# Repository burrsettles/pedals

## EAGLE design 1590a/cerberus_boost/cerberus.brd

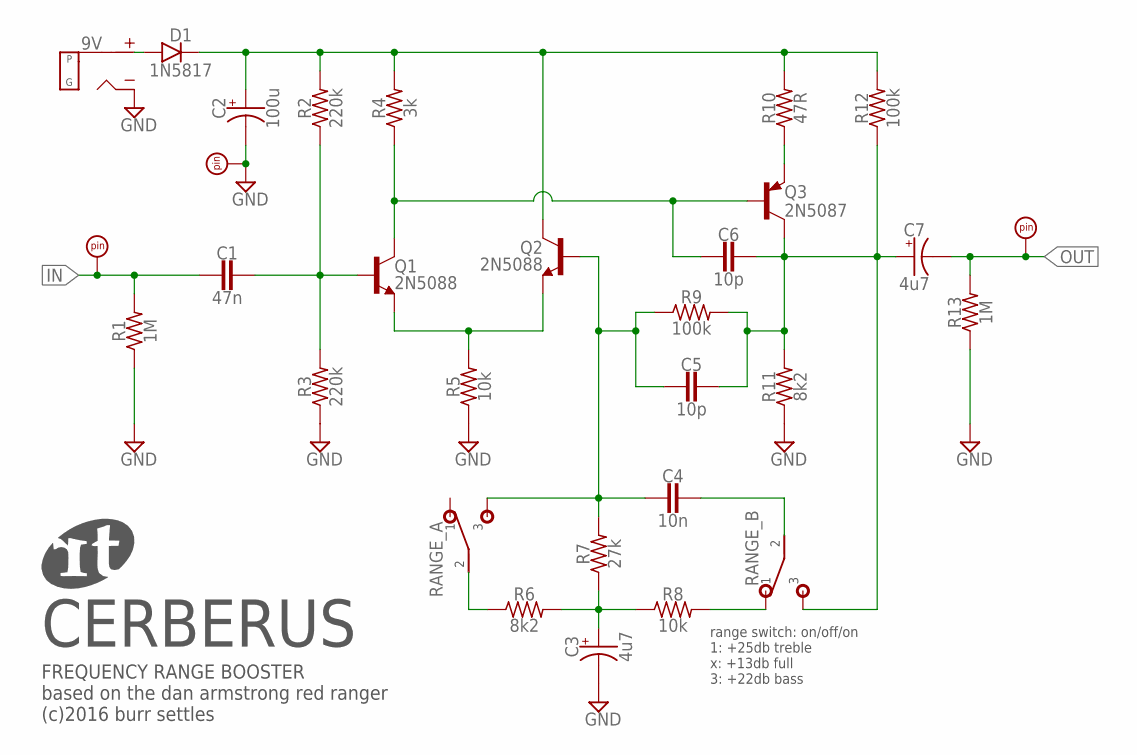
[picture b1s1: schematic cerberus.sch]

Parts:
9V: DC_MONO; DC
C1: 47n; BOX_SMALL
C2: 100u; 050_020_1
C3, C7: 4u7; 050_020_1
C4: 10n; BOX_SMALL
C5, C6: 10p; 050X030_025_2
D1: 1N5817; DO41-3
GND: PADRND; ROUND
IN: PADSQR; SQUARE
OUT: PADSQR; SQUARE
Q1, Q2: 2N5088; TO92-
Q3: 2N5087; TO92-
R1, R13: 1M; R0207/3
R2, R3: 220k; R0207/3
R4: 3k; R0207/3
R5, R8: 10k; R0207/3
R6, R11: 8k2; R0207/3
R7: 27k; R0207/3
R9, R12: 100k; R0207/3
R10: 47R; R0207/3
RANGE: DPDT; DPDT_PADS

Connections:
GND: 9V.S (SLEEVE), C2.-, C3.-, GND.1, R1.1, R3.1, R5.1, R11.1, R13.1
IN: C1.2, IN.1, R1.2
unnamed: C1.1, Q1.2 (B), R2.1, R3.2
unnamed: Q3.3 (E), R10.1
unnamed: 9V.T (TIP), D1.A
unnamed: C6.2, Q1.1 (C), Q3.2 (B), R4.1
unnamed: Q1.3 (E), Q2.3 (E), R5.2
unnamed: C5.1, C6.1, C7.+, Q3.1 (C), R9.2, R11.2, R12.1, RANGE.P$6 (3)
unnamed: C2.+, D1.C, Q2.1 (C), R2.2, R4.2, R10.2, R12.2
unnamed: R6.1, RANGE.P$2 (2)
unnamed: C4.1, RANGE.P$5 (2)
unnamed: C4.2, C5.2, Q2.2 (B), R7.2, R9.1, RANGE.P$3 (3)
unnamed: C3.+, R6.2, R7.1, R8.1
unnamed: R8.2, RANGE.P$4 (1)
OUT: C7.-, OUT.1, R13.2

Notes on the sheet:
CERBERUS
FREQUENCY RANGE BOOSTER based on the dan armstrong red ranger (c)2016 burr settles
range switch: on/off/on 1: +25db treble x: +13db full 3: +22db bass

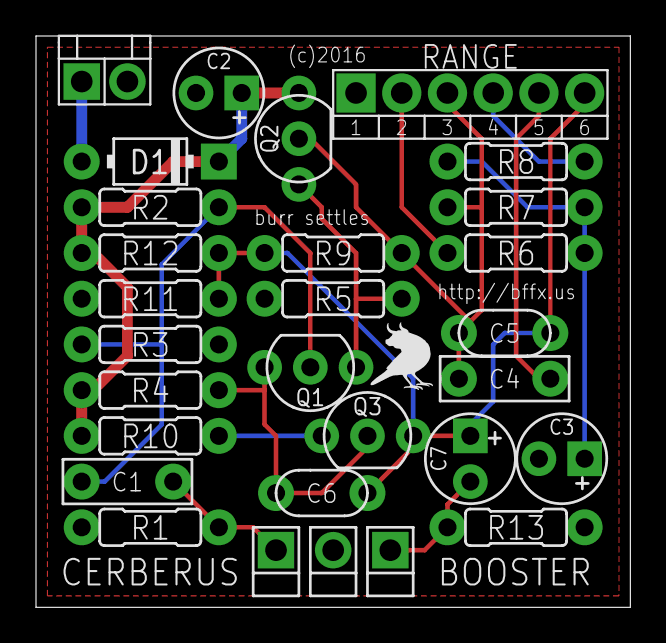
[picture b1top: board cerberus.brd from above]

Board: 2 copper layers, 33.0 x 31.7 mm, 30 parts (1 on the bottom side), 15 nets.

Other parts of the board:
U$1: BF0150

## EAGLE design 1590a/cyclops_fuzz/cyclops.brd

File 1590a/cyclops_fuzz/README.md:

# CYCLOPS

**MUFFLIKE FUZZ**

© 2016 Burr Settles ([LICENSE](../../LICENSE.md))

### overview

CYCLOPS is an in-your-face, no-holds-barred, wall-of-sound machine in a tiny little box. It is based on the [runoffgroove 22/7](http://runoffgroove.com/22-7.html), which in turn is a CMOS implementation of the [EHX Big Muff Pi](https://en.wikipedia.org/wiki/Big_Muff). However, CYCLOPS has been modified to have nothing but a VOLUME control: the tone stack has been removed (no more scooped mids!), and the gain/sustain is designed to be an internal trimmer; just to "set it and forget it" to taste.

### notes

* The clipping diodes (D1-D4) can be anything you want, though 1N914 is common in BMP clones. In my build, I ended up using 3mm red LEDs for D1-D2, and 1N4148s for D3-D4.
* The GAIN knob is layed out as a trimmer, but you can wire it to an offboard pot if you prefer.
* IC1 pins 2, 4, 13, and 16 are not connected.

### bill of materials

Qty | Parts | Value
--- | ----- | -----
1 | C1 | 47n film
1 | C2 | 100u electrolytic
1 | C3 | 220p ceramic
5 | C4, C5, C7, C9, C11 | 100n film
3 | C6, C8, C10 | 150p ceramic
4 | D1, D2, D3, D4 | your choice
1 | D5 | 1N5417
1 | IC1 | CD4049 hex-inverting buffer
3 | R1, R2, R9 | 100k
4 | R3, R6, R8, R11 | 1M
1 | R4 | 1k
2 | R5, R7 | 33k
1 | R10 | 330k
1 | GAIN | 100kA (trimmer)
1 | VOLUME | 100kA

### schematic

### layout

1.3" x 1.46" (1590a)

### build pic

18 June 2016

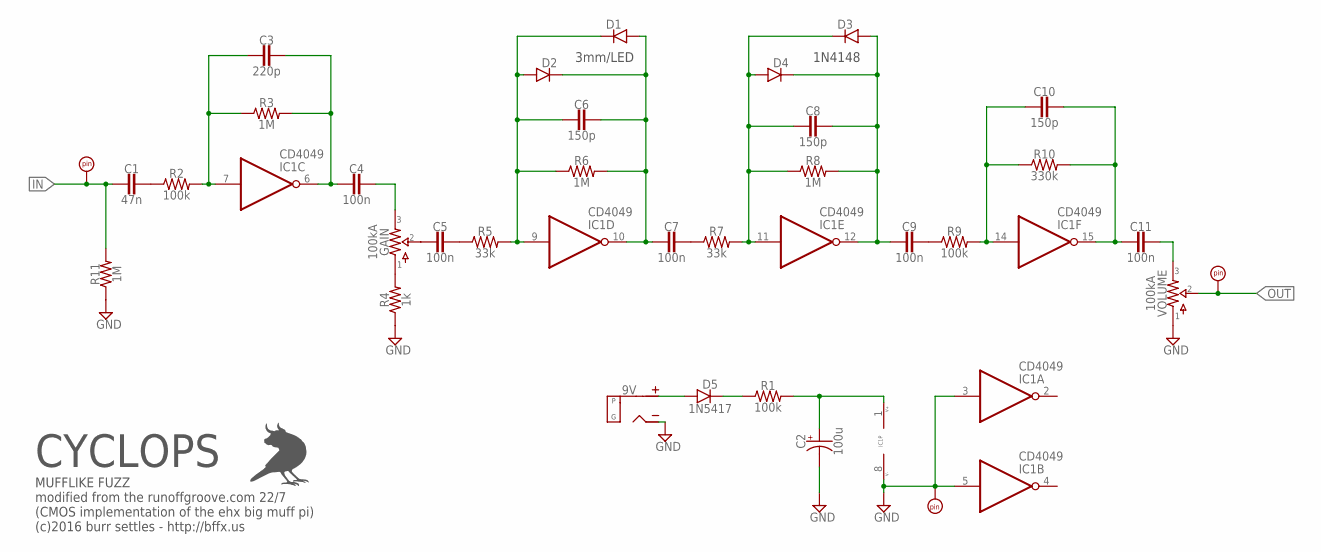
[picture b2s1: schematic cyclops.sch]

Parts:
9V: DC_MONO; DC
C1: 47n; 050X030_025_2
C2: 100u; 063_025
C3: 220p; 050X030_025_2
C4, C5, C7, C9, C11: 100n; 050X030_025_2
C6, C8, C10: 150p; 050X030_025_2
D1, D2, D3, D4: DO41.2; DO41-2
D5: 1N5417; DO41-3
GAIN: 100kA; 2262_TRIM
GND: PADRND; ROUND
IC1: CD4049; DIL16
IN: PADSQR; SQUARE
OUT: PADSQR; SQUARE
R1, R2, R9: 100k; R0207/2V
R3, R6, R8, R11: 1M; R0207/2V
R4: 1k; R0207/2V
R5, R7: 33k; R0207/2V
R10: 330k; R0207/2V
VOLUME: 100kA; PADS_SMALL

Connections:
GND: 9V.S (SLEEVE), C2.-, GND.1, IC1.3 (I), IC1.5 (I), IC1.8 (VSS), R4.1, R11.1, VOLUME.1
IN: C1.2, IN.1, R11.2
unnamed: C3.1, C4.2, IC1.6 (O), R3.2
unnamed: C5.2, GAIN.2
unnamed: C3.2, IC1.7 (I), R2.2, R3.1
unnamed: C1.1, R2.1
unnamed: C5.1, R5.1
unnamed: C6.2, D1.C, D2.A, IC1.9 (I), R5.2, R6.1
unnamed: C6.1, C7.2, D1.A, D2.C, IC1.10 (O), R6.2
unnamed: C7.1, R7.1
unnamed: C8.2, D3.C, D4.A, IC1.11 (I), R7.2, R8.1
unnamed: C4.1, GAIN.3
unnamed: C8.1, C9.2, D3.A, D4.C, IC1.12 (O), R8.2
unnamed: C9.1, R9.1
unnamed: C10.2, IC1.14 (I), R9.2, R10.1
unnamed: C10.1, C11.2, IC1.15 (O), R10.2
unnamed: GAIN.1, R4.2
unnamed: C11.1, VOLUME.3
unnamed: 9V.T (TIP), D5.A
unnamed: C2.+, IC1.1 (VDD), R1.2
unnamed: D5.C, R1.1
OUT: OUT.1, VOLUME.2

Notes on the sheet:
3mm/LED
1N4148
CYCLOPS
MUFFLIKE FUZZ modified from the runoffgroove.com 22/7 (CMOS implementation of the ehx big muff pi) (c)2016 burr settles - http://bffx.us

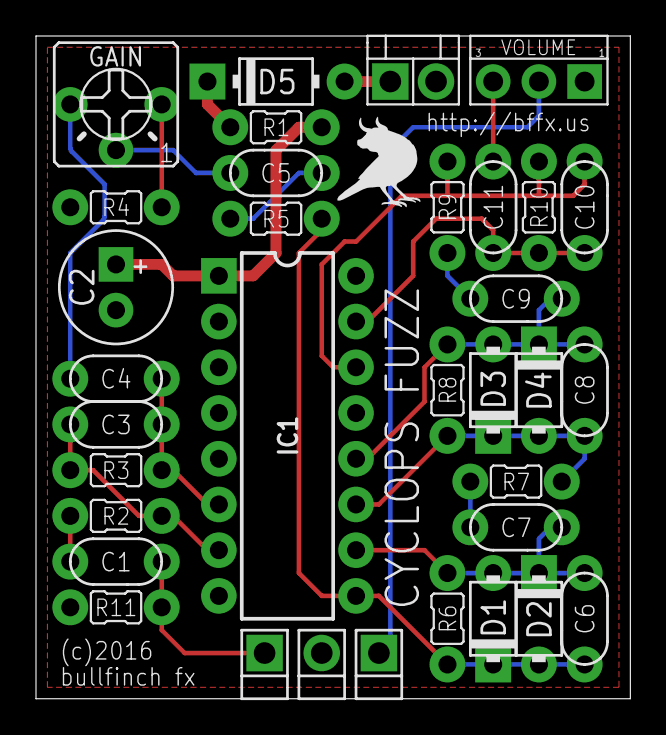
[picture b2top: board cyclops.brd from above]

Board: 2 copper layers, 33.0 x 36.8 mm, 35 parts (1 on the bottom side), 22 nets.

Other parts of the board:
U$3: BF0200

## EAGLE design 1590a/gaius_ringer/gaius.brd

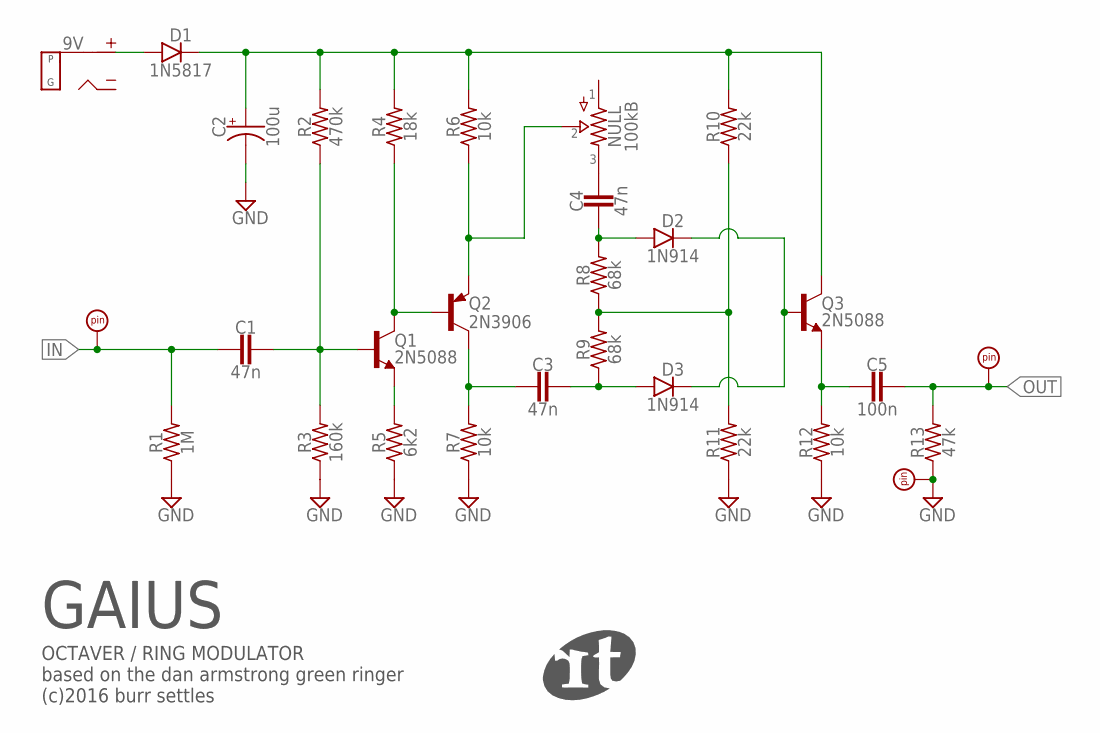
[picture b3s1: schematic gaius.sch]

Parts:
9V: DC_MONO; DC
C1, C3, C4: 47n; 050X030_025_2
C2: 100u; 050_020_1
C5: 100n; 050X030_025_2
D1: 1N5817; DO41-3
D2, D3: 1N914; DO35-2
GND: PADRND; ROUND
IN: PADSQR; SQUARE
NULL: 100kB; 2262_TRIM
OUT: PADSQR; SQUARE
Q1, Q3: 2N5088; TO92-
Q2: 2N3906; TO92-
R1: 1M; R0207/3
R2: 470k; R0207/3
R3: 160k; R0207/3
R4: 18k; R0207/3
R5: 6k2; R0207/3
R6, R7, R12: 10k; R0207/3
R8, R9: 68k; R0207/3
R10, R11: 22k; R0207/3
R13: 47k; R0207/3

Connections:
GND: C2.-, GND.1, R1.1, R3.1, R5.1, R7.1, R11.1, R12.1, R13.1
IN: C1.2, IN.1, R1.2
unnamed: Q1.1 (C), Q2.2 (B), R4.1
unnamed: Q1.3 (E), R5.2
unnamed: C1.1, Q1.2 (B), R2.1, R3.2
unnamed: C4.2, D2.A, R8.2
unnamed: NULL.2, Q2.3 (E), R6.1
unnamed: R8.1, R9.2, R10.1, R11.2
unnamed: C4.1, NULL.3
unnamed: C3.2, Q2.1 (C), R7.2
unnamed: C3.1, D3.A, R9.1
unnamed: C5.2, Q3.3 (E), R12.2
unnamed: D2.C, D3.C, Q3.2 (B)
unnamed: C2.+, D1.C, Q3.1 (C), R2.2, R4.2, R6.2, R10.2
unnamed: 9V.T (TIP), D1.A
OUT: C5.1, OUT.1, R13.2

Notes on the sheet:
GAIUS
OCTAVER / RING MODULATOR based on the dan armstrong green ringer (c)2016 burr settles

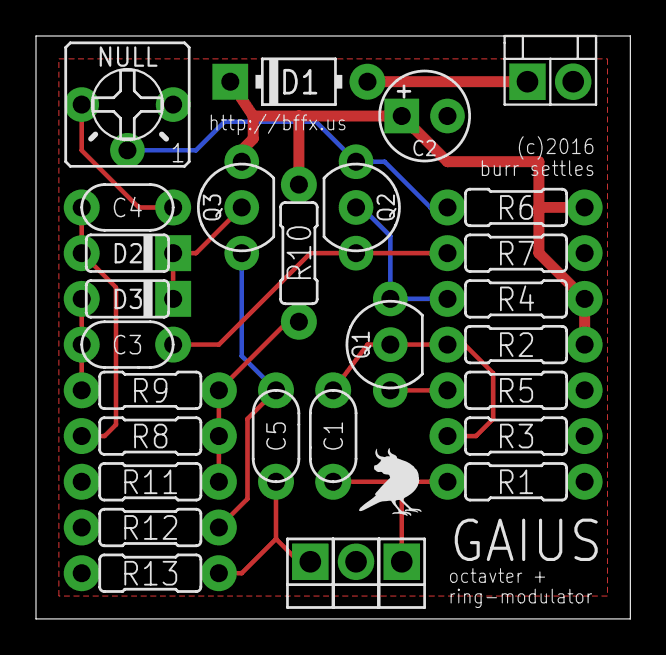
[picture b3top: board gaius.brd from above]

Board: 2 copper layers, 33.0 x 32.4 mm, 30 parts (1 on the bottom side), 16 nets.

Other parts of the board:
U$1: BF0150

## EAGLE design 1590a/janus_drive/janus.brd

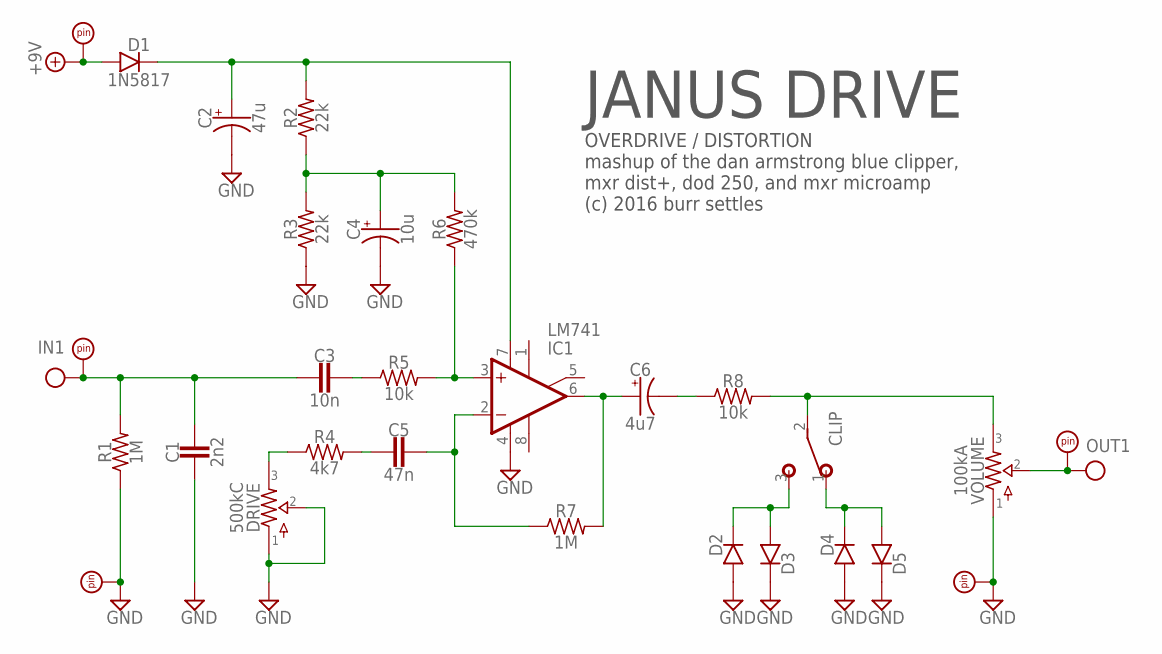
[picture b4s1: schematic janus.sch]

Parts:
C1: 2n2; BOX_SMALL
C2: 47u; 050_020_1
C3: 10n; BOX_SMALL
C4: 10u; 050_020_1
C5: 47n; BOX_SMALL
C6: 4u7; 050_020_1
CLIP: SPDTPADS; SPDT
D1: 1N5817; DO41-2
D2, D3: DO35.2; DO35-2
D4, D5: DO35.3; DO35-3
DRIVE: 500kC; PADS_SMALL
IC1: LM741; DIL08
PAD1, PAD2, PAD5: PADSQR; SQUARE
PAD3, PAD4: PADRND; ROUND
R1, R7: 1M; R0207/3
R2, R3: 22k; R0207/3
R4: 4k7; R0207/3
R5, R8: 10k; R0207/3
R6: 470k; R0207/3
VOLUME: 100kA; PADS_SMALL

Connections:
+9V: D1.A, PAD1.1
CLIP: CLIP.2, R8.2, VOLUME.3
GND: C1.1, C2.-, C4.-, D2.A, D3.C, D4.A, D5.C, DRIVE.1, DRIVE.2, IC1.4 (V-), PAD3.1, PAD4.1, R1.1, R3.1, VOLUME.1
IN: C1.2, C3.2, PAD2.1, R1.2
unnamed: C3.1, R5.1
unnamed: IC1.3 (+IN), R5.2, R6.1
unnamed: C5.1, IC1.2 (-IN), R7.1
unnamed: C5.2, R4.2
unnamed: C6.+, IC1.6 (OUT), R7.2
unnamed: C6.-, R8.1
unnamed: CLIP.3 (S), D2.C, D3.A
unnamed: C4.+, R2.1, R3.2, R6.2
unnamed: CLIP.1 (O), D4.C, D5.A
unnamed: DRIVE.3, R4.1
unnamed: C2.+, D1.C, IC1.7 (V+), R2.2
OUT: PAD5.1, VOLUME.2

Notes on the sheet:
JANUS DRIVE
OVERDRIVE / DISTORTION mashup of the dan armstrong blue clipper, mxr dist+, dod 250, and mxr microamp (c) 2016 burr settles

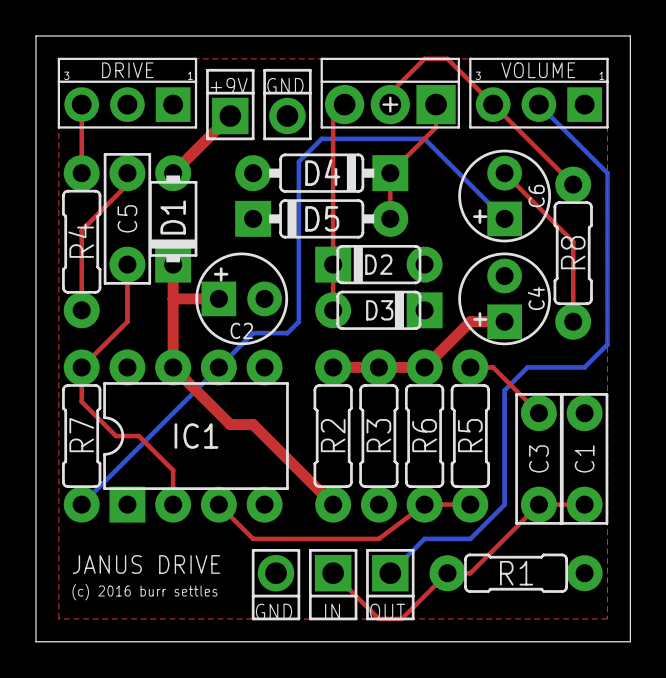
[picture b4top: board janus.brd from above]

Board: 2 copper layers, 33.0 x 33.7 mm, 28 parts (1 on the bottom side), 16 nets.

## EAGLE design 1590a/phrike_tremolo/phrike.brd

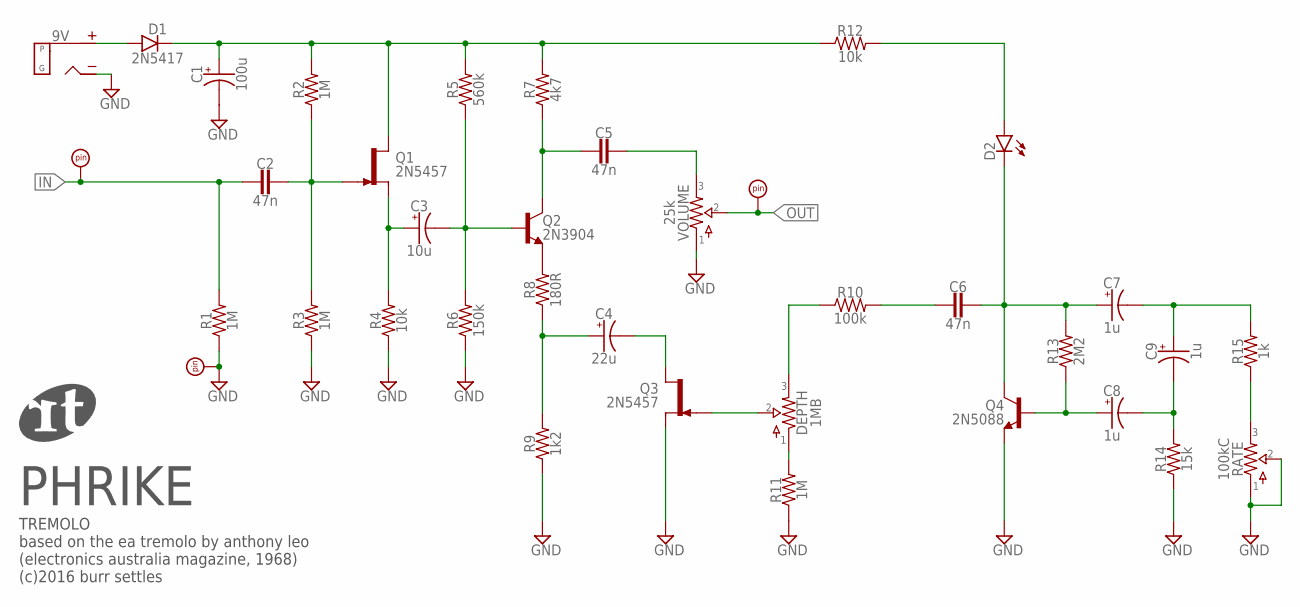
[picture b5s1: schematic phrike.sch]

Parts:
9V: DC_MONO; DC
C1: 100u; 063_025
C2, C5, C6: 47n; 050X030_025_2
C3: 10u; 050_020_1
C4: 22u; 050_020_1
C7, C8, C9: 1u; 050_020_1
D1: 2N5417; DO41-3
D2: LEDA; 3MM_A
DEPTH: 1MB; 2262_TRIM
GND: PADRND; ROUND
IN: PADSQR; SQUARE
OUT: PADSQR; SQUARE
Q1, Q3: 2N5457; TO92-
Q2: 2N3904; TO92-L2
Q4: 2N5088; TO92-
R1, R2, R3, R11: 1M; R0207/3
R4, R12: 10k; R0207/3
R5: 560k; R0207/3
R6: 150k; R0207/3
R7: 4k7; R0207/3
R8: 180R; R0207/3
R9: 1k2; R0207/3
R10: 100k; R0207/3
R13: 2M2; R0207/3
R14: 15k; R0207/3
R15: 1k; R0207/3
RATE: 100kC; PADS_SMALL
VOLUME: 25k; 2262_TRIM

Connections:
+9V: 9V.T (TIP), D1.A
GND: 9V.S (SLEEVE), C1.-, GND.1, Q3.2 (S), Q4.3 (E), R1.1, R3.1, R4.1, R6.1, R9.1, R11.1, R14.1, RATE.1, RATE.2, VOLUME.1
IN: C2.2, IN.1, R1.2
unnamed: C2.1, Q1.1 (G), R2.1, R3.2
unnamed: C3.+, Q1.2 (S), R4.2
unnamed: C3.-, Q2.2 (B), R5.1, R6.2
unnamed: C5.2, Q2.1 (C), R7.1
unnamed: Q2.3 (E), R8.2
unnamed: C5.1, VOLUME.3
unnamed: C1.+, D1.C, Q1.3 (D), R2.2, R5.2, R7.2, R12.1
unnamed: C4.+, R8.1, R9.2
unnamed: C4.-, Q3.3 (D)
unnamed: DEPTH.2, Q3.1 (G)
unnamed: DEPTH.3, R10.1
unnamed: C6.2, R10.2
unnamed: C6.1, C7.+, D2.K (C), Q4.1 (C), R13.2
unnamed: C8.+, Q4.2 (B), R13.1
unnamed: C7.-, C9.+, R15.2
unnamed: C8.-, C9.-, R14.2
unnamed: DEPTH.1, R11.2
unnamed: R15.1, RATE.3
unnamed: D2.A, R12.2
OUT: OUT.1, VOLUME.2

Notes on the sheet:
PHRIKE
TREMOLO based on the ea tremolo by anthony leo (electronics australia magazine, 1968) (c)2016 burr settles

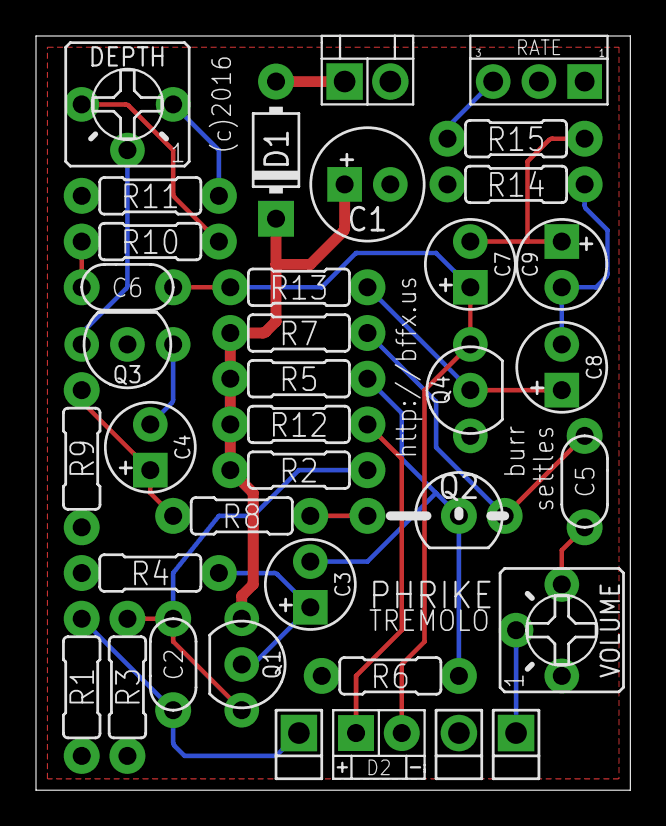
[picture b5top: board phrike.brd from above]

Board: 2 copper layers, 33.0 x 41.9 mm, 38 parts (1 on the bottom side), 23 nets.

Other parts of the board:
U$1: BF0150

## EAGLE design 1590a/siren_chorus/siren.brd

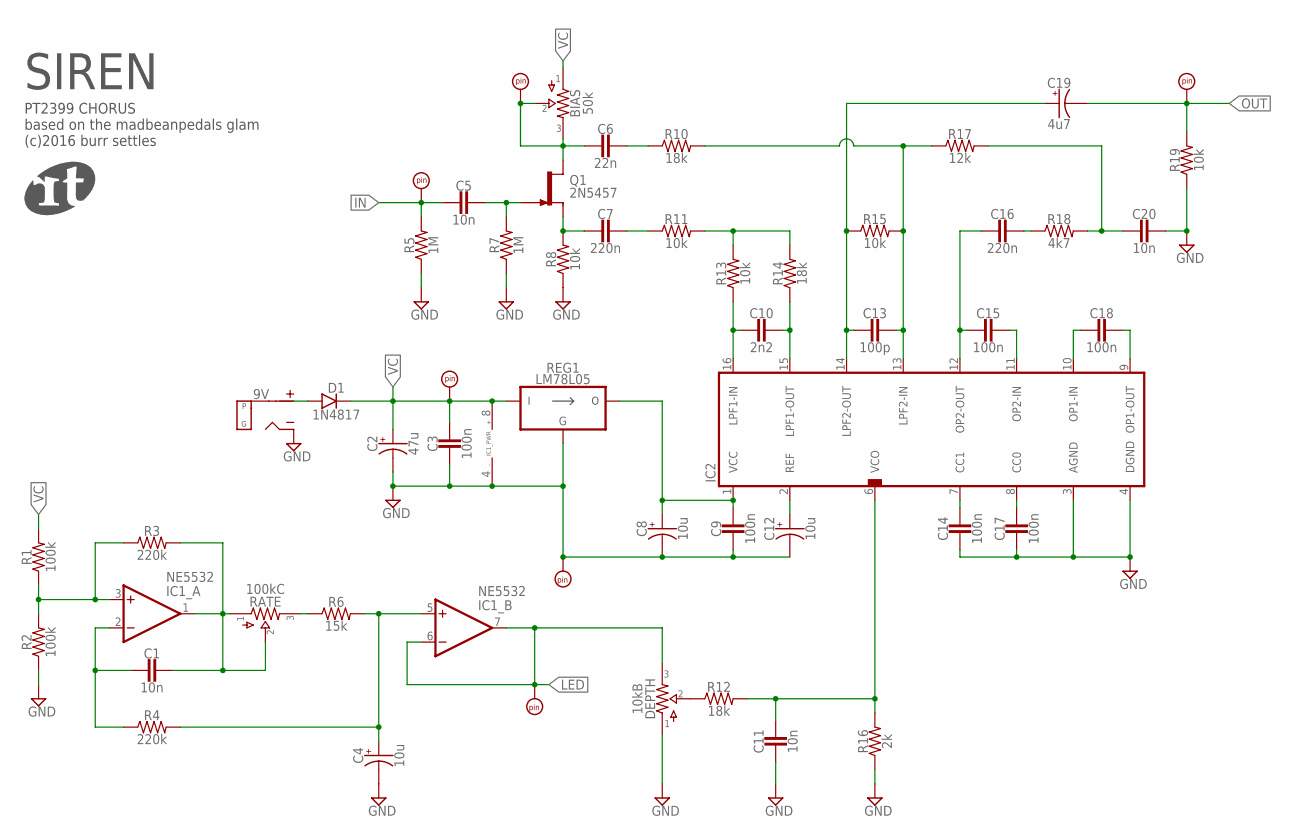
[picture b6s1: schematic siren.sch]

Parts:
9V: DC_MONO; DC
BIAS: 50k; 2262_TRIM
C1, C5, C11, C20: 10n; 050X030_025_2
C2: 47u; 050_020_1
C3, C9, C14, C15, C17, C18: 100n; 050X030_025_2
C4, C12: 10u; 050_020_1
C6: 22n; 050X030_025_2
C7, C16: 220n; 050X030_025_2
C8: 10u; 050_020
C10: 2n2; 050X030_025_2
C13: 100p; 050X030_025_2
C19: 4u7; 050_020_1
D1: 1N4817; DO41-3
DEPTH: 10kB; 2262_TRIM
GND: PADRND; ROUND
IC1: NE5532; DIL08
IC2: PT2399TH; DIL16
IN: PADSQR; SQUARE
L+: PADSQR; SQUARE
OUT: PADSQR; SQUARE
PAD1, PAD2: PAD; UNLABELED
Q1: 2N5457; TO92-
R1, R2: 100k; R0207/2V
R3, R4: 220k; R0207/2V
R5, R7: 1M; R0207/2V
R6: 15k; R0207/2V
R8, R11, R13, R15, R19: 10k; R0207/2V
R10, R12, R14: 18k; R0207/2V
R16: 2k; R0207/2V
R17: 12k; R0207/2V
R18: 4k7; R0207/2V
RATE: 100kC; PADS_SMALL
REG1: LM78L05; TO92-

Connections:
+9V: 9V.T (TIP), D1.A
GND: 9V.S (SLEEVE), C2.-, C3.2, C4.-, C8.-, C9.2, C11.2, C12.-, C14.2, C17.2, C20.1, DEPTH.1, GND.1, IC1.4 (V-), IC2.3 (AGND), IC2.4 (DGND), R2.1, R5.1, R7.1, R8.1, R16.1, R19.1, REG1.2 (GND)
IN: C5.2, IN.1, R5.2
LED: DEPTH.3, IC1.6 (-IN), IC1.7 (OUT), L+.1
unnamed: C13.1, IC2.13 (LPF2-IN), R10.2, R15.2, R17.1
unnamed: C8.+, C9.1, IC2.1 (VCC), REG1.3 (VO)
unnamed: C10.2, IC2.16 (LPF1-IN), R13.1
unnamed: C10.1, IC2.15 (LPF1-OUT), R14.1
unnamed: C20.2, R17.2, R18.2
unnamed: C12.+, IC2.2 (REF)
unnamed: C14.1, IC2.7 (CC1)
unnamed: C17.1, IC2.8 (CC0)
unnamed: C15.1, IC2.11 (OP2-IN)
unnamed: C18.2, IC2.10 (OP1-IN)
unnamed: C18.1, IC2.9 (OP1-OUT)
unnamed: C13.2, C19.+, IC2.14 (LPF2-OUT), R15.1
unnamed: R11.2, R13.2, R14.2
unnamed: C7.1, R11.1
unnamed: C7.2, Q1.2 (S), R8.2
unnamed: C6.1, R10.1
unnamed: BIAS.2, BIAS.3, C6.2, PAD2.P$1, Q1.3 (D)
unnamed: C5.1, Q1.1 (G), R7.2
unnamed: IC1.3 (+IN), R1.1, R2.2, R3.1
unnamed: C15.2, C16.2, IC2.12 (OP2-OUT)
unnamed: C16.1, R18.1
unnamed: C1.1, IC1.1 (OUT), R3.2, RATE.1, RATE.2
unnamed: C1.2, IC1.2 (-IN), R4.1
unnamed: DEPTH.2, R12.1
unnamed: R6.1, RATE.3
unnamed: C4.+, IC1.5 (+IN), R4.2, R6.2
unnamed: C11.1, IC2.6 (VCO), R12.2, R16.2
OUT: C19.-, OUT.1, R19.2
VC: BIAS.1, C2.+, C3.1, D1.C, IC1.8 (V+), PAD1.P$1, R1.2, REG1.1 (VI)

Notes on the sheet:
PT2399 CHORUS based on the madbeanpedals glam (c)2016 burr settles
SIREN

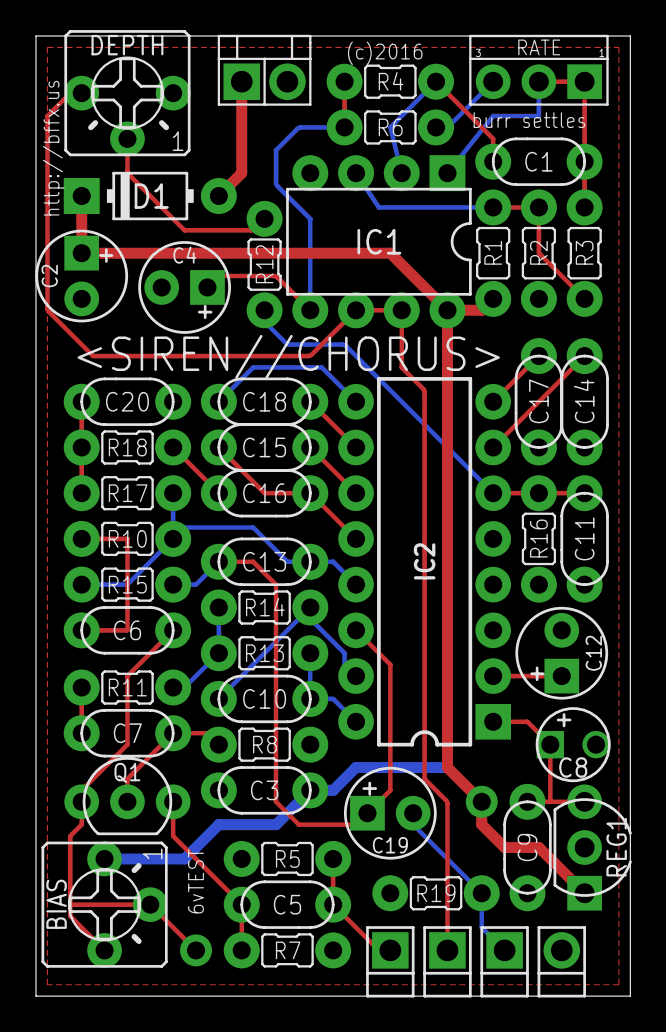
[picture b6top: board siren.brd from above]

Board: 2 copper layers, 33.0 x 53.3 mm, 54 parts (1 on the bottom side), 33 nets.

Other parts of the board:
U$1: BF0150

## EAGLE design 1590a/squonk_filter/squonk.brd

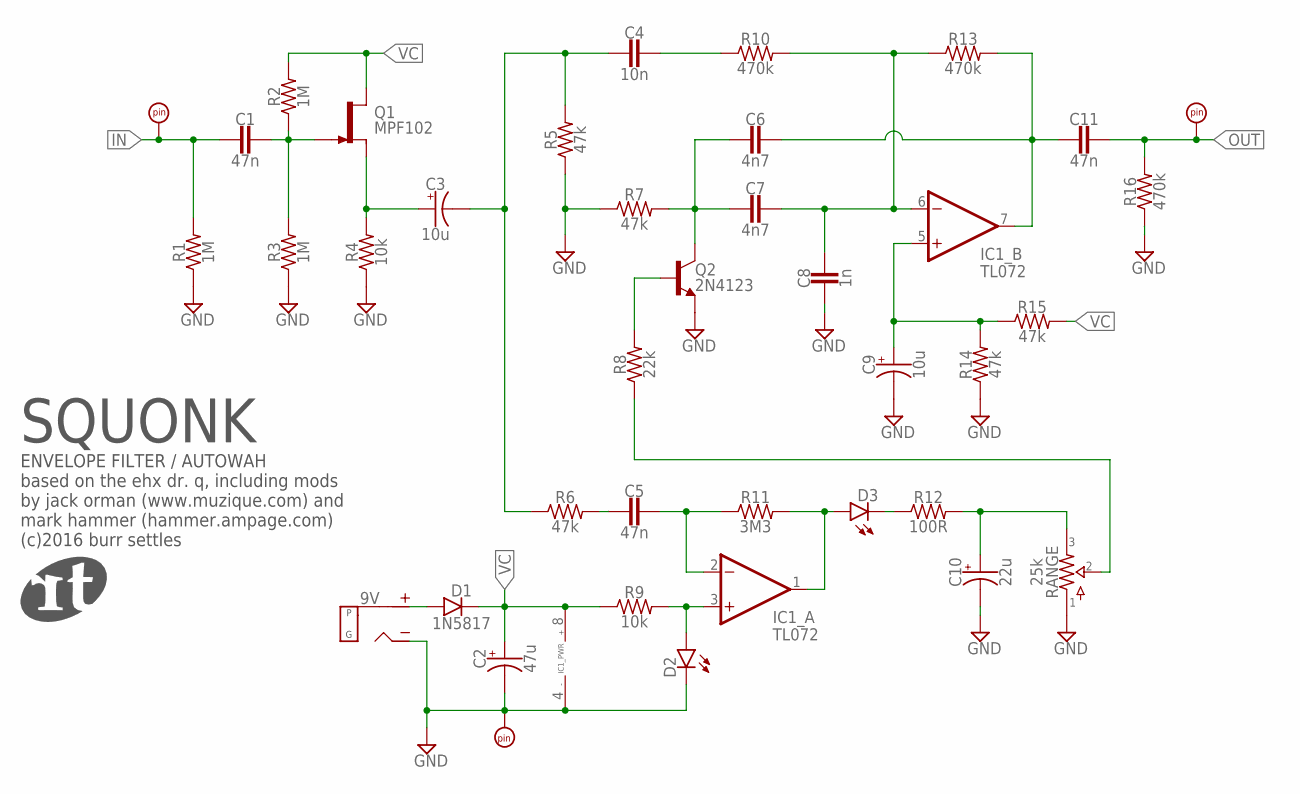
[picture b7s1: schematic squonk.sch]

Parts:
9V: DC_MONO; DC
C1, C5, C11: 47n; 050X030_025_2
C2: 47u; 050_020_1
C3, C9: 10u; 050_020_1
C4: 10n; 050X030_025_2
C6, C7: 4n7; 050X030_025_2
C8: 1n; 050X030_025_2
C10: 22u; 050_020_1
D1: 1N5817; DO41-3
D2, D3: LEDB; 3MM_B
GND: PADRND; ROUND
IC1: TL072; DIL08
IN: PADSQR; SQUARE
OUT: PADSQR; SQUARE
Q1: MPF102; TO92-
Q2: 2N4123; TO92-
R1, R2, R3: 1M; R0207/3
R4, R9: 10k; R0207/3
R5, R6, R7, R14, R15: 47k; R0207/3
R8: 22k; R0207/3
R10, R13, R16: 470k; R0207/3
R11: 3M3; R0207/3
R12: 100R; R0207/3
RANGE: 25k; PADS_SMALL

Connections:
GND: 9V.S (SLEEVE), C2.-, C8.2, C9.-, C10.-, D2.K (C), GND.1, IC1.4 (V-), Q2.3 (E), R1.1, R3.1, R4.1, R5.1, R7.1, R14.1, R16.1, RANGE.1
IN: C1.2, IN.1, R1.2
unnamed: C1.1, Q1.1 (G), R2.1, R3.2
unnamed: C3.+, Q1.2 (S), R4.2
unnamed: C3.-, C4.2, R5.2, R6.1
unnamed: C5.2, R6.2
unnamed: D2.A, IC1.3 (+IN), R9.2
unnamed: C5.1, IC1.2 (-IN), R11.1
unnamed: D3.A, IC1.1 (OUT), R11.2
unnamed: D3.K (C), R12.1
unnamed: C10.+, R12.2, RANGE.3
unnamed: 9V.T (TIP), D1.A
unnamed: C7.1, C8.1, IC1.6 (-IN), R10.2, R13.1
unnamed: Q2.2 (B), R8.2
unnamed: R8.1, RANGE.2
unnamed: C6.2, C7.2, Q2.1 (C), R7.2
unnamed: C6.1, C11.2, IC1.7 (OUT), R13.2
unnamed: C4.1, R10.1
unnamed: C9.+, IC1.5 (+IN), R14.2, R15.1
OUT: C11.1, OUT.1, R16.2
VC: C2.+, D1.C, IC1.8 (V+), Q1.3 (D), R2.2, R9.1, R15.2

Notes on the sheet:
SQUONK
ENVELOPE FILTER / AUTOWAH based on the ehx dr. q, including mods by jack orman (www.muzique.com) and mark hammer (hammer.ampage.com) (c)2016 burr settles

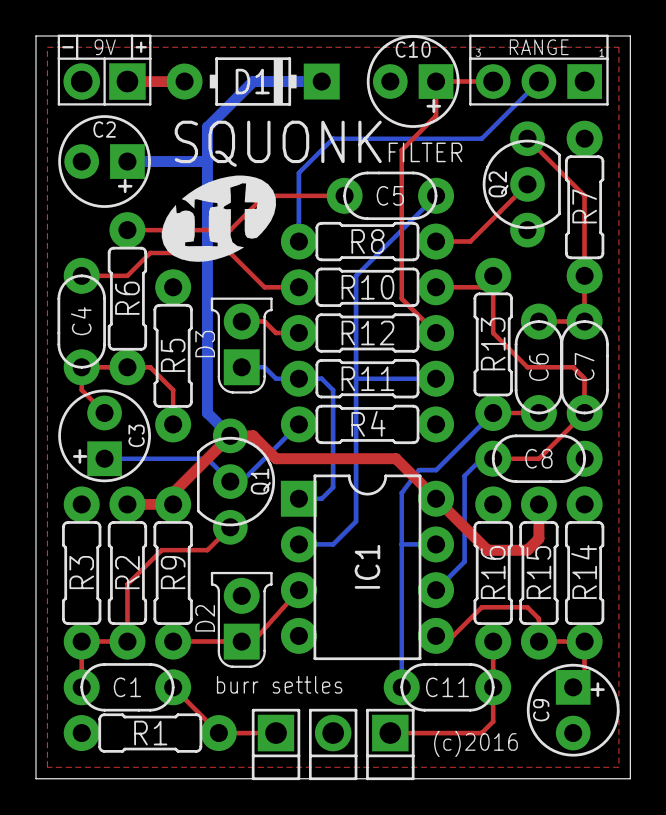
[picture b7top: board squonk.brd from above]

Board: 2 copper layers, 33.0 x 41.3 mm, 39 parts (0 on the bottom side), 21 nets.

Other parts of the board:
U$1: RT0250
